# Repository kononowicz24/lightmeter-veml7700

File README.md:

A lightmeter for an analog camera powered by a Infenion XMC2GO board. Features 5 buttons, OLED screen with reading and a VEML7700 light meter IC. The device is powered from a LIR2032 Li-ion cell in a standard form factor.

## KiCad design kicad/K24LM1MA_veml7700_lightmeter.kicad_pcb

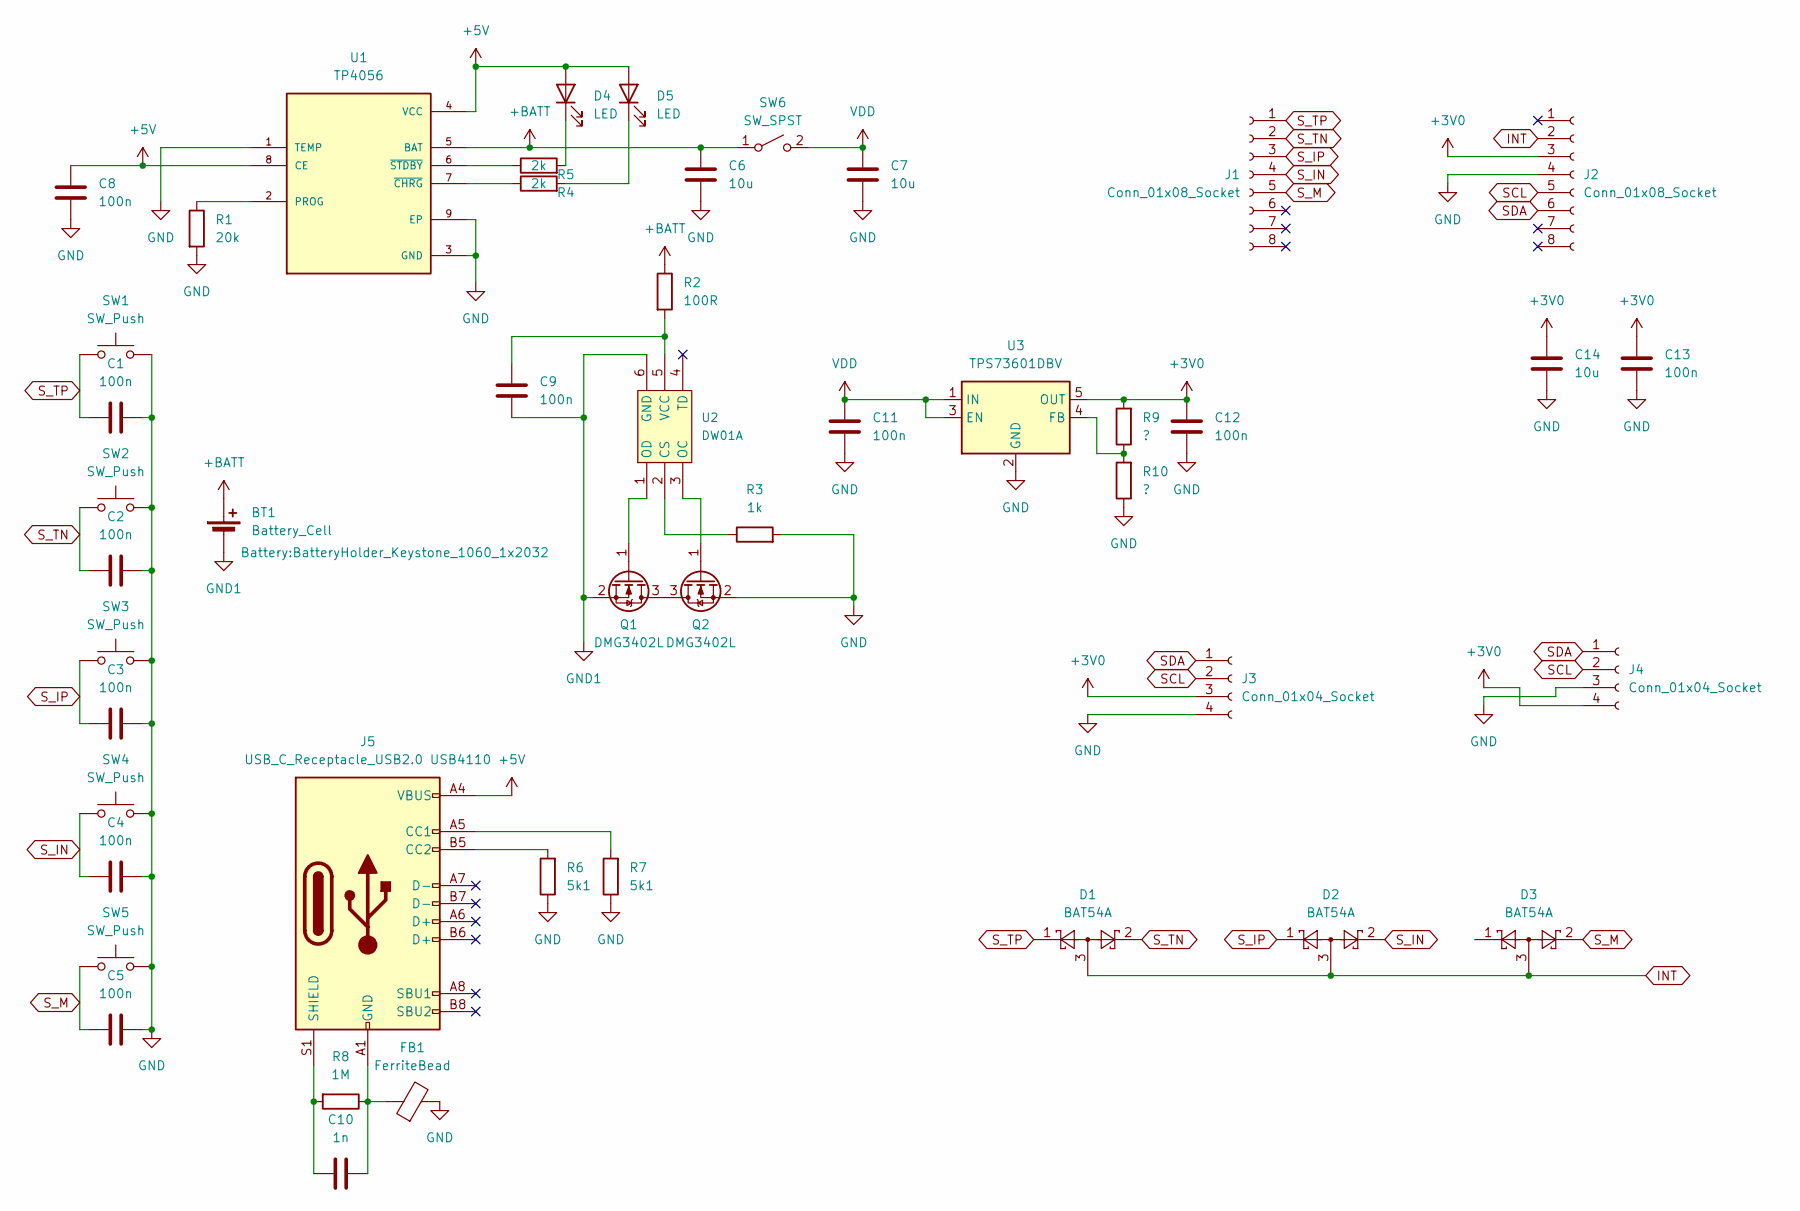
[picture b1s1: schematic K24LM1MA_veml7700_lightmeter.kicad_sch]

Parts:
BT1: Battery_Cell; BatteryHolder_Keystone_1060_1x2032
C1, C2, C3, C4, C5, C8, C9, C11, C12, C13: 100n; C_0603_1608Metric
C6, C7, C14: 10u; C_0603_1608Metric
C10: 1n; C_0603_1608Metric
D1, D2, D3: BAT54A; SOT-23
D4, D5: LED; LED_0603_1608Metric
FB1: FerriteBead; L_0603_1608Metric
J1, J2: Conn_01x08_Socket; PinHeader_1x08_P2.54mm_Vertical
J3, J4: Conn_01x04_Socket; PinHeader_1x04_P2.54mm_Vertical
J5: USB_C_Receptacle_USB2.0 USB4110; USB_C_Receptacle_GCT_USB4110
Q1, Q2: DMG3402L; SOT-23
R1: 20k; R_0603_1608Metric
R2: 100R; R_0603_1608Metric
R3: 1k; R_0603_1608Metric
R4, R5: 2k; R_0603_1608Metric
R6, R7: 5k1; R_0603_1608Metric
R8: 1M; R_0603_1608Metric
R9, R10: ?; R_0603_1608Metric
SW1, SW2, SW3, SW4, SW5: SW_Push; SW_Push_1P1T_NO_CK_KSC7xxJ
SW6: SW_SPST; SW_SPDT_PCM12
U1: TP4056; SOP127P600X175-9N
U2: DW01A; SOT-23-6
U3: TPS73601DBV; SOT-23-5

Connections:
+3V0: C12.2, C13.2, C14.2, J2.3, J3.3, J4.4, R9.2, U3.5 (OUT)
+5V: C8.2, D4.2 (A), D5.2 (A), J5.A4 (VBUS), J5.A9 (VBUS), J5.B4 (VBUS), J5.B9 (VBUS), U1.4 (VCC), U1.8 (CE)
+BATT: BT1.1 (+), C6.2, R2.1, SW6.1 (A), U1.5 (BAT)
GND: C1.2, C2.2, C3.2, C4.2, C5.2, C6.1, C7.1, C8.1, C11.1, C12.1, C13.1, C14.1, FB1.2, J2.4, J3.4, J4.3, Q2.2 (S), R1.2, R3.2, R6.1, R7.1, R10.1, SW1.2, SW2.2, SW3.2, SW4.2, SW5.2, U1.1 (TEMP), U1.3 (GND), U1.9 (EP), U3.2 (GND)
GND1: BT1.2 (-), C9.1, Q1.2 (S), U2.6 (GND)
INT: D1.3, D2.3, D3.3, J2.2
unnamed: C10.1, FB1.1, J5.A1 (GND), J5.A12 (GND), J5.B1 (GND), J5.B12 (GND), R8.1
unnamed: D4.1 (K), R5.2
unnamed: D5.1 (K), R4.2
unnamed: J5.A5 (CC1), R7.2
unnamed: J5.B5 (CC2), R6.2
unnamed: C10.2, J5.S1 (SHIELD), R8.2
unnamed: Q1.3 (D), Q2.3 (D)
unnamed: Q1.1 (G), U2.1 (OD)
unnamed: Q2.1 (G), U2.3 (OC)
unnamed: R1.1, U1.2 (PROG)
unnamed: R4.1, U1.7 (~CHRG)
unnamed: R5.1, U1.6 (~STDBY)
unnamed: R3.1, U2.2 (CS)
unnamed: C9.2, R2.2, U2.5 (VCC)
unnamed: R9.1, R10.2, U3.4 (FB)
SCL: J2.5, J3.2, J4.2
SDA: J2.6, J3.1, J4.1
S_IN: C4.1, D2.2, J1.4, SW4.1
S_IP: C3.1, D2.1, J1.3, SW3.1
S_M: C5.1, D3.2, J1.5, SW5.1
S_TN: C2.1, D1.2, J1.2, SW2.1
S_TP: C1.1, D1.1, J1.1, SW1.1
VDD: C7.2, C11.2, SW6.2 (B), U3.1 (IN), U3.3 (EN)

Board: 2 copper layers, 47 parts (8 on the bottom side), 29 nets, no tracks yet.

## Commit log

2023-06-03 deleted SW buttons, added IRQ for buttons, discarded incompatible concurrency library
2023-06-07 added routines for shutter speed buttons, added aperture calculation
2023-12-30 added kicad gitignore
2023-12-31 added PCB sch
2024-01-06 layout components, switches changed to smd
2024-01-07 finished layout, generated gerber files
